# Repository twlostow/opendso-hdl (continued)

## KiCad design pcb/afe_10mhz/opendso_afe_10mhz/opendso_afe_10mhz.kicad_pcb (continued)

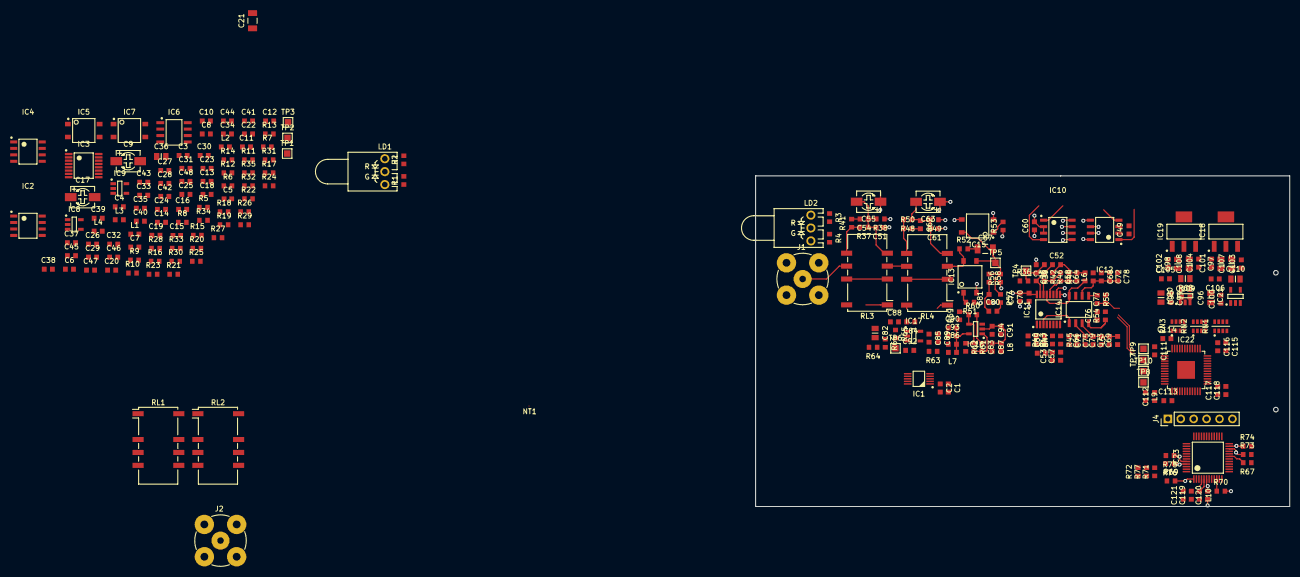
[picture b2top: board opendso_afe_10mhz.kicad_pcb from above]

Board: 4 copper layers, 105.0 x 65.0 mm, 255 parts (1 on the bottom side), 169 nets.

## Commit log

2019-04-24 hdl: initial commit
2019-05-18 pcb: AFE 1st kicad version
2019-05-19 AFE schematic: finished port to KiCad
2019-05-19 AFE: added review notes document
2019-05-24 pcb: added lcd_test_board design
2019-06-04 pcb/lcd_test_board: update
2019-06-05 hdl: clean up local copy of MIPI DSI core, include Vivado Tcl
2019-06-05 ip_cores: updated to latest version of MIPI DSI
2019-06-09 hdl: updated dsi-core submodule
2019-06-16 opendso_top: project TCL files & synced-up submodules
2019-07-06 top: fix color format configuration for v_frmbuf_rd, added GPIO reset line
2019-07-06 hdl: updated submodules
